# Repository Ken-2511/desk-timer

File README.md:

# desk-timer

使用 Arduino Nano 制作的桌面计时器，同时用于学习 KiCad 原理图和 PCB 设计。

## 第一版功能

- 固定计时 25 分钟。
- 6 颗 LED 显示剩余进度。
- 两个按钮分别用于开始／暂停、复位计时。
- 计时结束后由无源压电蜂鸣器提示，可通过程序改变音调。
- 通过 Nano 的 USB 接口供电和下载程序。

## 元器件清单

当前采用 **TDK PS1240P02BT 压电式无源蜂鸣器**方案；电阻和两颗电容均采用 1206 贴片封装，其余元件的安装方式见表。

| 元件 | 数量 | 型号／电气规格 | 封装／尺寸与安装方式 | 备注 |
|---|---:|---|---|---|
| Arduino Nano | 1 | 暂按经典款 5V／ATmega328P Nano v3.x | 已焊排针，插装到排母 | 用户已有；具体型号、引脚定义和两排间距待确认 |
| Nano 排母 | 2 | 单排 1×15Pin，间距 2.54mm | 直插；两排中心距暂按 15.24mm | 焊在底板上，用于插拔 Nano |
| 绿色 LED | 6 | 例如 Kingbright WP7113GD，雾面绿色 | 直径 5mm、两脚直插、脚距 2.54mm | 进度指示；每颗单独串联一个限流电阻 |
| LED 限流电阻 | 6 | 680Ω，¼W | 1206 贴片，约 3.2×1.6mm | 按经典款 5V Nano 设计 |
| 轻触按钮 | 2 | Omron B3F-1000，常开瞬时按钮 | 6×6mm、四脚直插、孔位 6.5×4.5mm | 开始／暂停、复位计时；四脚对应两个电气端子 |
| 压电式无源蜂鸣器 | 1 | TDK PS1240P02BT，外部方波驱动 | 直径 12.2mm、高 6.5mm、两脚直插、脚距 5mm | 提示音先按约 4kHz；实际响度待样机确认 |
| 蜂鸣器串联限流电阻 | 1 | 330Ω，¼W | 1206 贴片 | 限制 GPIO 切换时的瞬态电流 |
| 蜂鸣器隔直电容 | 1 | 1µF，非极性，耐压 ≥16V | X7R 陶瓷、1206 贴片 | 与 330Ω 串联；采购时匹配容量、耐压和封装 |
| 蜂鸣器泄放电阻 | 1 | 100kΩ，¼W | 1206 贴片 | 并联在蜂鸣器两端 |
| 电源去耦电容 | 1 | 100nF，非极性，耐压 ≥16V | X7R 陶瓷、1206 贴片 | 跨接 5V 与 GND；采购时匹配容量、耐压和封装 |
| USB 数据线 | 1 | 与现有 Nano 的 USB 接口匹配 | 板外配件 | 需要支持数据传输，供电和下载程序共用 |

该方案不再使用此前电磁蜂鸣器方案中的 BC337、220Ω 基极电阻、10kΩ 基极下拉电阻和 1N4007 续流二极管。

## KiCad 符号与封装

以下条目已在本机 KiCad 10 自带库中找到；电容及 Nano 的最终封装仍须与采购件／实物核对。

| 元件 | Symbol | Footprint | 匹配说明 |
|---|---|---|---|
| Nano 及其排母安装位置 | `MCU_Module:Arduino_Nano_v3.x` | `Module:Arduino_Nano` | 整体封装包含两排各 15 个焊孔，可用于安装两条排母，不再重复放置两套排母封装 |
| LED | `Device:LED` | `LED_THT:LED_D5.0mm` | 脚距 2.54mm；1 为阴极、2 为阳极 |
| 所有 1206 电阻 | `Device:R` | `Resistor_SMD:R_1206_3216Metric_Pad1.30x1.75mm_HandSolder` | 加长焊盘，方便手焊；阻值分别填 680Ω、330Ω、100kΩ |
| 按钮 | `Switch:SW_Push` | `Button_Switch_THT:SW_TH_Tactile_Omron_B3F-100x` | 对应 B3F-1000；封装中两对焊盘分别共用编号 1、2 |
| 压电蜂鸣器 | `Device:Buzzer` | `Buzzer_Beeper:Buzzer_TDK_PS1240P02BT_D12.2mm_H6.5mm` | 型号对应的专用封装，脚距 5mm |
| 1µF 隔直电容 | `Device:C` | `Capacitor_SMD:C_1206_3216Metric_Pad1.33x1.80mm_HandSolder` | 已选用 1206 手焊封装 |
| 100nF 去耦电容 | `Device:C` | `Capacitor_SMD:C_1206_3216Metric_Pad1.33x1.80mm_HandSolder` | 与 C1 相同的 1206 手焊封装 |

上述标准库元件直接引用 KiCad 自带库；当前不需要复制到项目专用库。

## 蜂鸣器驱动接法

```text
Nano GPIO ── 330Ω ── 1µF ──┬── PS1240P02BT ── GND
                           └── 100kΩ ───────── GND
```

这是本项目拟采用的 GPIO 驱动方案，并非照搬厂商参考电路：串联电容隔直，100kΩ 电阻提供电荷泄放通路，330Ω 电阻限制切换瞬间的电流；按 5V 电平跳变估算约为 15mA。

程序使用 `tone()` 输出约 4kHz 方波，停止提示时结束方波输出；实际响度、波形及 GPIO 负载在样机阶段确认。

## 待确认事项

- 用户现有 Nano 是否为经典款 5V／ATmega328P，以及排针方向、排距和 USB 接口类型。
- 两种电容的实际采购型号；均按 1206、X7R、耐压 ≥16V 选购，容量分别为 1µF 和 100nF。
- 已完成原理图、PCB 布局与布线；尚未生成生产文件或制作样机。

## 参考资料

- [TDK PS 系列数据手册：尺寸、外部激励方式及避免直流偏置的要求](https://product.tdk.com/info/en/catalog/datasheets/piezoelectronic_buzzer_ps_en.pdf)
- [Kingbright WP7113GD 数据手册](https://www.kingbrightusa.com/images/catalog/spec/wp7113gd.pdf)
- [Omron B3F 系列数据手册](https://omronfs.omron.com/en_US/ecb/products/pdf/en-b3f.pdf)

## LED 与 GPIO 对应

PCB 上 D1–D6 从左到右排列，分别经 R1–R6 连接 Nano 的 D7、D6、D5、D4、D3、D2；这一顺序用于减少布线交叉。
固件中从左到右的 LED 引脚数组应为 `{7, 6, 5, 4, 3, 2}`。

## PCB 布线配置

- 80 × 50 mm 双层板；保留当前元件布局。
- 默认信号线宽 0.30 mm；5V 和 GND 的 Power 网络类线宽 0.50 mm；铜间距 0.25 mm。
- 过孔直径 0.80 mm、钻孔 0.40 mm；铜到板边至少 0.50 mm。
- 主要连线在顶层；底层两段短跳线，其余以连续 GND 铺铜为主；共 5 个过孔。
- 底层 GND 区采用热焊盘连接，间隙及连接桥宽均为 0.30 mm，并移除孤立铜岛。
- 本次填充铜区后 DRC：0 违规、0 未连接；焊盘网络与原理图一致。

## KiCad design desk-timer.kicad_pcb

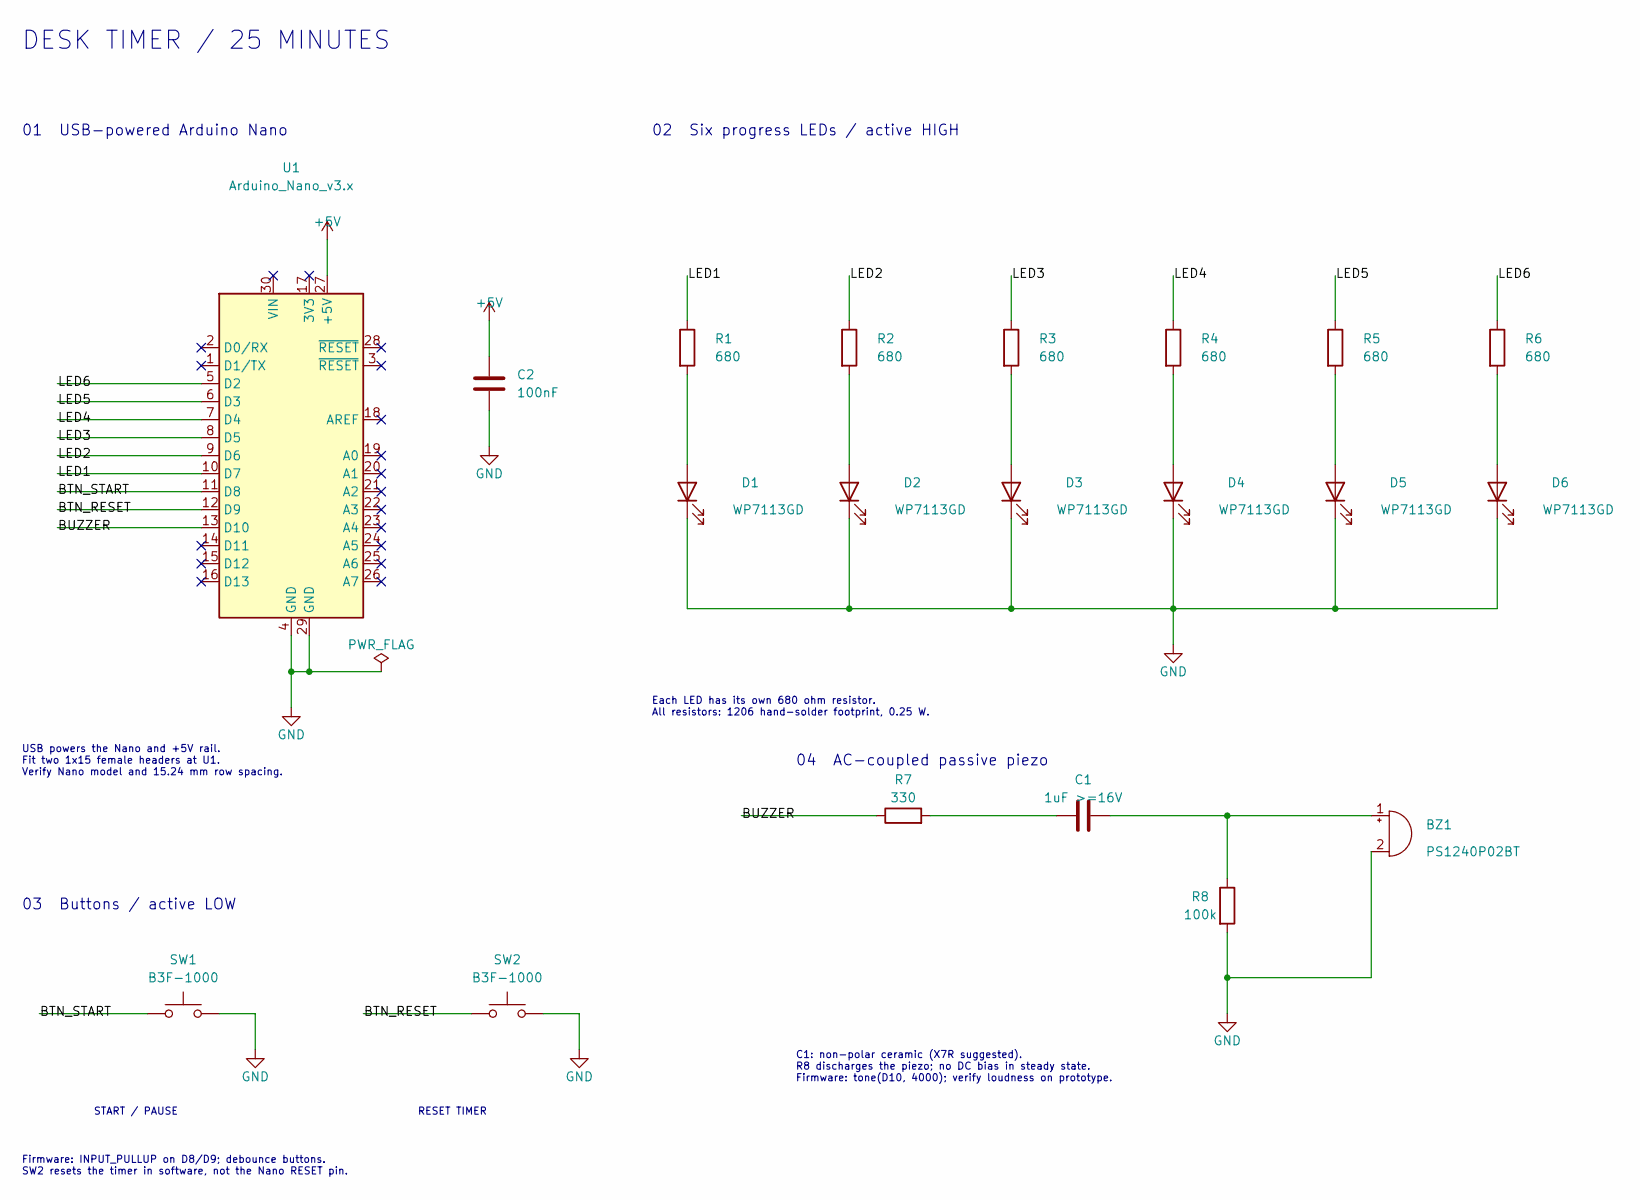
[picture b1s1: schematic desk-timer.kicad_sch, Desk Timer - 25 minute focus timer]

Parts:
BZ1: PS1240P02BT; Buzzer_TDK_PS1240P02BT_D12.2mm_H6.5mm
C1: 1uF >=16V; C_1206_3216Metric_Pad1.33x1.80mm_HandSolder
C2: 100nF; C_1206_3216Metric_Pad1.33x1.80mm_HandSolder
D1, D2, D3, D4, D5, D6: WP7113GD; LED_D5.0mm
R1, R2, R3, R4, R5, R6: 680; R_1206_3216Metric_Pad1.30x1.75mm_HandSolder
R7: 330; R_1206_3216Metric_Pad1.30x1.75mm_HandSolder
R8: 100k; R_1206_3216Metric_Pad1.30x1.75mm_HandSolder
SW1, SW2: B3F-1000; SW_TH_Tactile_Omron_B3F-100x
U1: Arduino_Nano_v3.x; Arduino_Nano

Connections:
+5V: C2.1, U1.27 (+5V)
/BTN_RESET: SW2.1, U1.12 (D9)
/BTN_START: SW1.1, U1.11 (D8)
/BUZZER: R7.1, U1.13 (D10)
/LED1: R1.1, U1.10 (D7)
/LED2: R2.1, U1.9 (D6)
/LED3: R3.1, U1.8 (D5)
/LED4: R4.1, U1.7 (D4)
/LED5: R5.1, U1.6 (D3)
/LED6: R6.1, U1.5 (D2)
GND: BZ1.2 (-), C2.2, D1.1 (K), D2.1 (K), D3.1 (K), D4.1 (K), D5.1 (K), D6.1 (K), R8.2, SW1.2, SW2.2, U1.4 (GND), U1.29 (GND)
unnamed: BZ1.1 (+), C1.2, R8.1
unnamed: C1.1, R7.2
unnamed: D1.2 (A), R1.2
unnamed: D2.2 (A), R2.2
unnamed: D3.2 (A), R3.2
unnamed: D4.2 (A), R4.2
unnamed: D5.2 (A), R5.2
unnamed: D6.2 (A), R6.2

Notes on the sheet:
DESK TIMER / 25 MINUTES
01 USB-powered Arduino Nano
USB powers the Nano and +5V rail. Fit two 1x15 female headers at U1. Verify Nano model and 15.24 mm row spacing.
02 Six progress LEDs / active HIGH
Each LED has its own 680 ohm resistor. All resistors: 1206 hand-solder footprint, 0.25 W.
03 Buttons / active LOW
START / PAUSE
RESET TIMER
Firmware: INPUT_PULLUP on D8/D9; debounce buttons. SW2 resets the timer in software, not the Nano RESET pin.
04 AC-coupled passive piezo
C1: non-polar ceramic (X7R suggested). R8 discharges the piezo; no DC bias in steady state. Firmware: tone(D10, 4000); verify loudness on prototype.

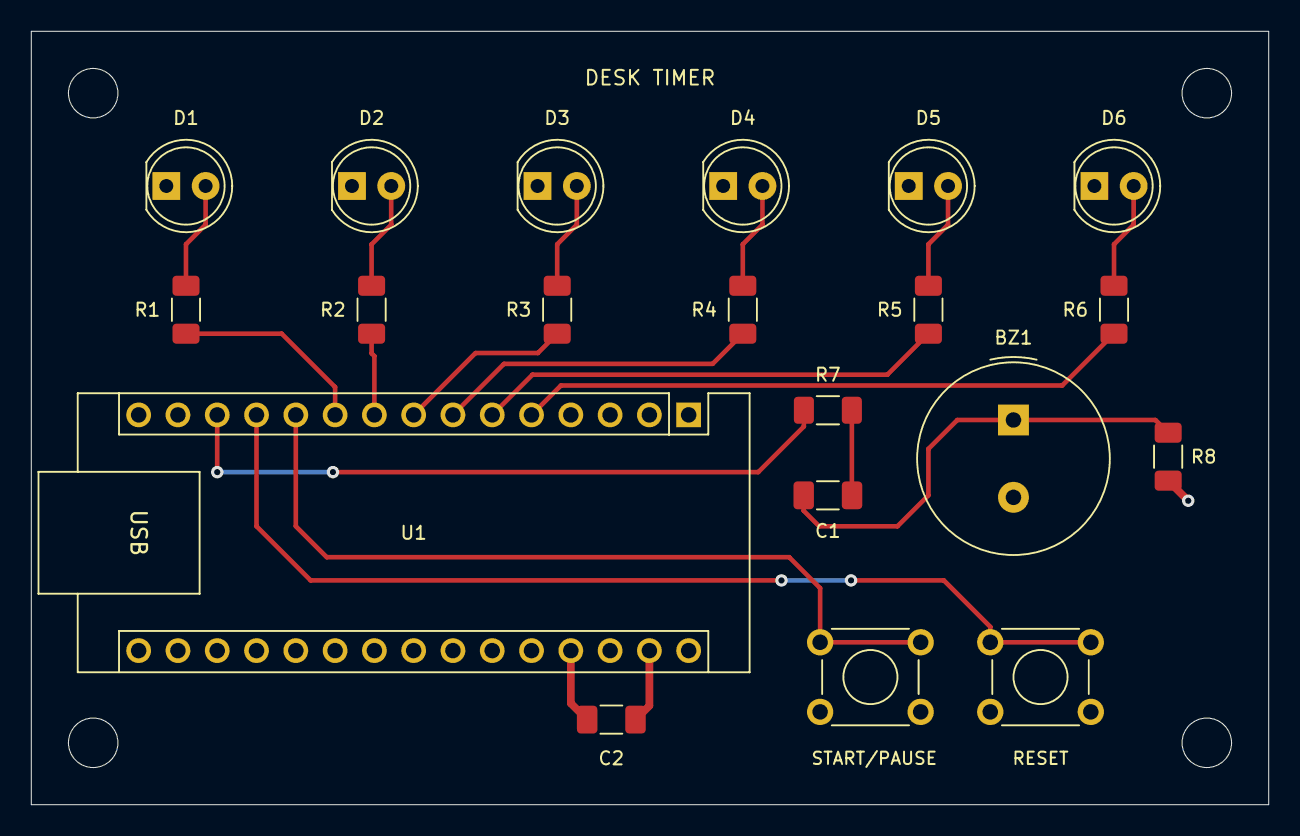
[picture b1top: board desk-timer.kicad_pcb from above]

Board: 2 copper layers, 80.0 x 50.0 mm, 24 parts (0 on the bottom side), 19 nets.

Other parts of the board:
H1, H2, H3, H4: MountingHole_3.2mm_M3

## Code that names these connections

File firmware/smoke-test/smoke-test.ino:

// desk-timer smoke test: LED chaser (跑马灯) plus button and buzzer checks.
//
// - LEDs D1-D6 chase left to right, bouncing back at each end.
// - SW1 (start/pause, D8) pauses or resumes the chaser.
// - SW2 (reset, D9) jumps back to the leftmost LED.
// - The buzzer (D10) beeps once at power-up and on every button press.

const uint8_t LED_PINS[] = {7, 6, 5, 4, 3, 2};  // D1..D6, left to right
const uint8_t LED_COUNT = sizeof(LED_PINS) / sizeof(LED_PINS[0]);

const uint8_t BTN_START = 8;   // SW1, active LOW
const uint8_t BTN_RESET = 9;   // SW2, active LOW
const uint8_t BUZZER = 10;

const unsigned int BEEP_HZ = 4000;
const unsigned long STEP_MS = 120;
const unsigned long DEBOUNCE_MS = 30;

int8_t position = 0;
int8_t direction = 1;
bool paused = false;
unsigned long lastStep = 0;

struct Button {
  uint8_t pin;
  bool stableState;      // true = released (HIGH)
  bool lastReading;
  unsigned long changedAt;
};

Button startBtn = {BTN_START, true, true, 0};
Button resetBtn = {BTN_RESET, true, true, 0};

// Returns true once per press, after debouncing.
bool pressed(Button &b) {
  bool reading = digitalRead(b.pin);
  if (reading != b.lastReading) {
    b.lastReading = reading;
    b.changedAt = millis();
  }
  if (millis() - b.changedAt > DEBOUNCE_MS && reading != b.stableState) {
    b.stableState = reading;
    return reading == LOW;
  }
  return false;
}

void beep(unsigned long ms) {
  tone(BUZZER, BEEP_HZ, ms);
}

void showLed(int8_t index) {
  for (uint8_t i = 0; i < LED_COUNT; i++) {
    digitalWrite(LED_PINS[i], i == index ? HIGH : LOW);
  }
}

void setup() {
  for (uint8_t i = 0; i < LED_COUNT; i++) {
    pinMode(LED_PINS[i], OUTPUT);
  }
  pinMode(BTN_START, INPUT_PULLUP);
  pinMode(BTN_RESET, INPUT_PULLUP);
  pinMode(BUZZER, OUTPUT);

  // Power-up check: all LEDs on with a beep, then start chasing.
  for (uint8_t i = 0; i < LED_COUNT; i++) {
    digitalWrite(LED_PINS[i], HIGH);
  }
  beep(200);
  delay(500);
  showLed(position);
  lastStep = millis();
}

void loop() {
  if (pressed(startBtn)) {
    paused = !paused;
    beep(50);
  }
  if (pressed(resetBtn)) {
    position = 0;
    direction = 1;
    showLed(position);
    lastStep = millis();
    beep(50);
  }

  if (!paused && millis() - lastStep >= STEP_MS) {
    lastStep += STEP_MS;
    if (position + direction < 0 || position + direction >= LED_COUNT) {
      direction = -direction;
    }
    position += direction;
    showLed(position);
  }
}
